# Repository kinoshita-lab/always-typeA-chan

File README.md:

# always-typeA-chan

A converter circuit that always outputs type A TRS MIDI

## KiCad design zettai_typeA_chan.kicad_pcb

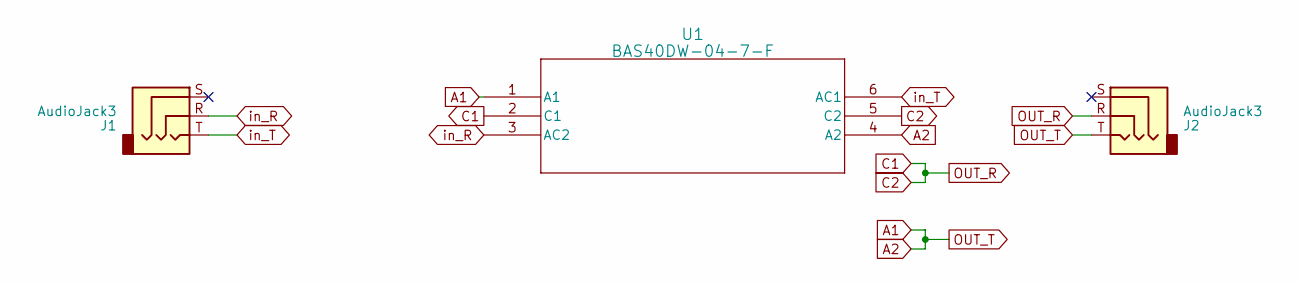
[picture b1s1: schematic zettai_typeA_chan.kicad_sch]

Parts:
J1, J2: AudioJack3; 3.5mm_Stereo_TRS_PJ-3210-4A_and_ST-005-G; LCSC C136686
U1: BAS40DW-04-7-F; SOT-363_DIO; LCSC C134364

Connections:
A1: J2.T, U1.1 (A1), U1.4 (A2)
C1: J2.R, U1.2 (C1), U1.5 (C2)
in_R: J1.R, U1.3 (AC2)
in_T: J1.T, U1.6 (AC1)

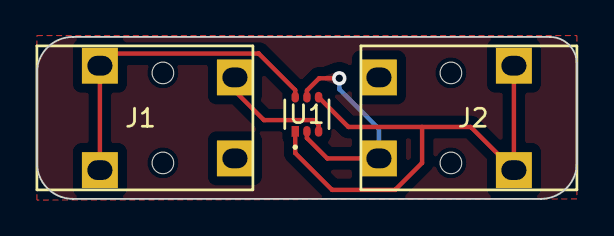
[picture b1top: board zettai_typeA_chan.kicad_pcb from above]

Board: 2 copper layers, 30.0 x 9.0 mm, 3 parts (0 on the bottom side), 4 nets.
